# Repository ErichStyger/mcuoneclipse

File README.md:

mcuoneclipse
============

McuOnEclipse Processor Expert components and example projects.
C:\ProgramData\Processor Expert\CWMCU_PE5_00\beans

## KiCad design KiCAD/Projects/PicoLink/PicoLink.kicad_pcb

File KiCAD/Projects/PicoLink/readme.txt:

KiCAD and enclosure design files for a RP2040 based debug probe (PicoLink).
See https://github.com/ErichStyger/mcuoneclipse/tree/master/KiCAD/Projects/PicoLink

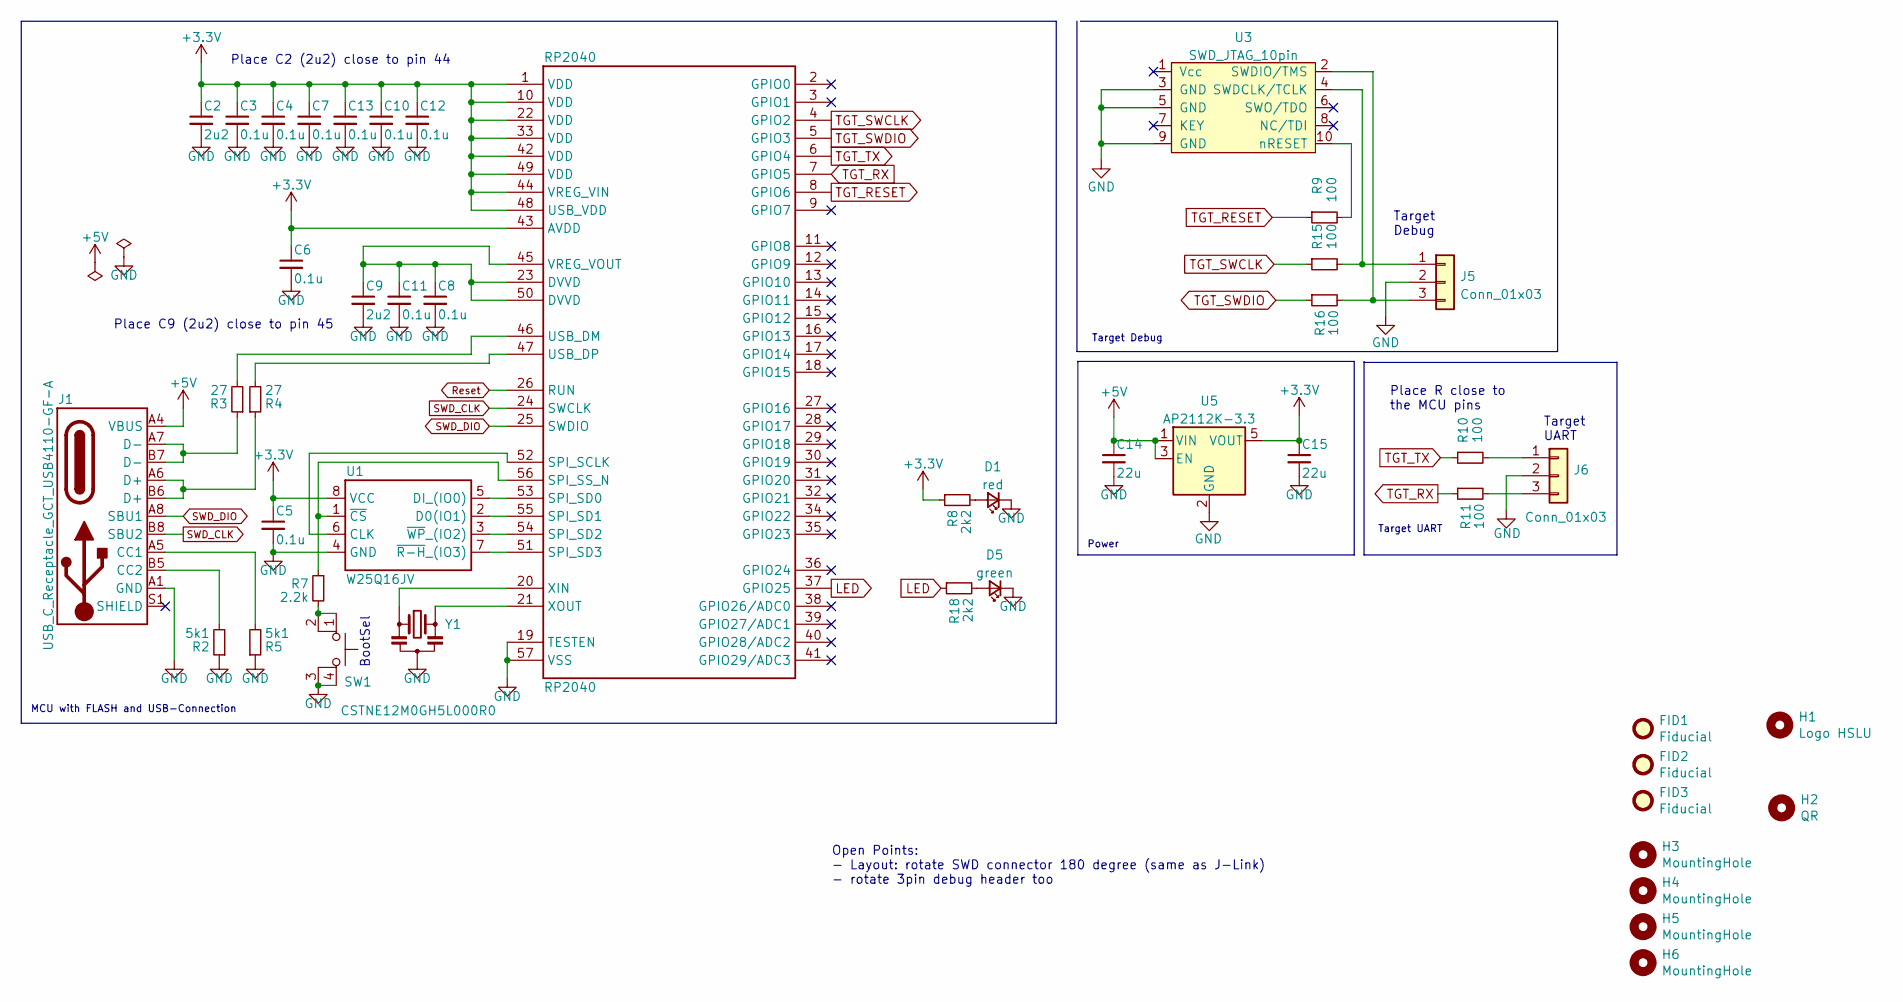
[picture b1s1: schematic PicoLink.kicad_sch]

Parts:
C2, C9: 2u2; C_0603_1608Metric; MFR# CC0402MRX5R6BB225; mouser# 603-CC402MRX5R6BB225
C3, C4, C6, C7, C8, C10, C11, C12, C13: 0.1u; C_0603_1608Metric; MFR# C0402C104K8RAC7867; mouser# 80-C0402C104K8R7867
C5: 0.1u; C_0603_1608Metric; MFR# CC0603KRX7R8BB104; mouser# 603-CC603KRX7R8BB104
C14, C15: 22u; C_0805; MFR# CL21A226MOQNNNE; mouser# 187-CL21A226MOQNNNE
D1: red; LED_0603
D5: green; LED_0603
FID1, FID2, FID3: Fiducial; Fiducial_1mm_Mask2mm
H1: Logo HSLU; Hochschule_Luzern_New
H2: QR; QR_McuOnEclipse_Silkscreen
H3, H4, H5, H6: MountingHole; MountingHole_2.7mm_M2.5
J1: USB_C_Receptacle_GCT_USB4110-GF-A; MFR# USB4110-GF-A; mouser# 640-USB4110-GF-A
J5, J6: Conn_01x03; PinHeader_1x03_P2.54mm_Vertical
R2, R5: 5k1; R_0603_1608Metric; MFR# RC0603JR-075K6L; mouser# 603-RC0603JR-075K6L
R3, R4: 27; R_0603_1608Metric; MFR# RC0603JR-0727RL; mouser# 603-RC0603JR-0727RL
R7: 2.2k; R_0603_1608Metric; MFR# RC0603JR-071KL; mouser# 603-RC0603JR-071KL
R8, R18: 2k2; R_0603_1608Metric; MFR# RC0603JR-071KL; mouser# 603-RC0603JR-071KL
R9, R10, R11, R15, R16: 100; R_0603_1608Metric; MFR# RC0603JR-071KL; mouser# 603-RC0603JR-071KL
RP2040: RP2040; QFN-56-1EP_7x7mm_P0.4mm_EP3.2x3.2mm; MFR# RPI Chip RP2040-7-500; mouser# 358-RP2040CHIP-7-500
SW1: 434123025826_BTN
U1: W25Q16JV; USON_2x3x0.6mm; MFR# W25Q16JVUXIQ TR; mouser# 454-W25Q16JVUXIQTR
U3: SWD_JTAG_10pin; SWD_Pin_Header_Straight_2x05_Pitch1.27mm_SMD
U5: AP2112K-3.3; IC-SOT25; mouser# 621-AP2112K-3.3TRG1
Y1: CSTNE12M0GH5L000R0; Resonator_SMD_Murata_CSTxExxV-3Pin_3.0x1.1mm; MFR# CSTNE12M0GH5L000R0; mouser# 81-CSTNE12M0GH5L000R

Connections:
+3.3V: C2.1, C3.1, C4.1, C5.1, C6.1, C7.1, C10.1, C12.1, C13.1, C15.1, R8.1, RP2040.1 (VDD), RP2040.10 (VDD), RP2040.22 (VDD), RP2040.33 (VDD), RP2040.42 (VDD), RP2040.43 (AVDD), RP2040.44 (VREG_VIN), RP2040.48 (USB_VDD), RP2040.49 (VDD), U1.8 (VCC), U5.5 (VOUT)
+5V: C14.1, J1.A4 (VBUS), J1.A9 (VBUS), J1.B4 (VBUS), J1.B9 (VBUS), U5.1 (VIN), U5.3 (EN)
GND: C2.2, C3.2, C4.2, C5.2, C6.2, C7.2, C8.2, C9.2, C10.2, C11.2, C12.2, C13.2, C14.2, C15.2, D1.1 (K), D5.1 (K), J1.A1 (GND), J1.A12 (GND), J1.B1 (GND), J1.B12 (GND), J5.2, J6.2, R2.1, R5.1, RP2040.19 (TESTEN), RP2040.57 (VSS), SW1.3 (K), SW1.4 (A), U1.4 (GND), U3.3 (GND), U3.5 (GND), U3.9 (GND), U5.2 (GND), Y1.2
LED: R18.1, RP2040.37 (GPIO25)
unnamed: C8.1, C9.1, C11.1, RP2040.23 (DVVD), RP2040.45 (VREG_VOUT), RP2040.50 (DVVD)
unnamed: D1.2 (A), R8.2
unnamed: D5.2 (A), R18.2
unnamed: J1.A5 (CC1), R5.2
unnamed: J1.A6 (D+), J1.B6 (D+), R4.1
unnamed: J1.A7 (D-), J1.B7 (D-), R3.1
unnamed: J1.B5 (CC2), R2.2
unnamed: J5.1, R15.2, U3.4 (SWDCLK/TCLK)
unnamed: J5.3, R16.2, U3.2 (SWDIO/TMS)
unnamed: J6.1, R10.2
unnamed: J6.3, R11.2
unnamed: R3.2, RP2040.46 (USB_DM)
unnamed: R4.2, RP2040.47 (USB_DP)
unnamed: R7.1, RP2040.56 (SPI_SS_N), U1.1 (~CS)
unnamed: R7.2, SW1.1, SW1.2
unnamed: R9.2, U3.10 (nRESET)
unnamed: RP2040.20 (XIN), Y1.1
unnamed: RP2040.21 (XOUT), Y1.3
unnamed: RP2040.51 (SPI_SD3), U1.7 (~R-H_(IO3))
unnamed: RP2040.52 (SPI_SCLK), U1.6 (CLK)
unnamed: RP2040.53 (SPI_SD0), U1.5 (DI_(IO0))
unnamed: RP2040.54 (SPI_SD2), U1.3 (~WP_(IO2))
unnamed: RP2040.55 (SPI_SD1), U1.2 (D0(IO1))
Reset: RP2040.26 (RUN)
SWD_CLK: J1.B8 (SBU2), RP2040.24 (SWCLK)
SWD_DIO: J1.A8 (SBU1), RP2040.25 (SWDIO)
TGT_RESET: R9.1, RP2040.8 (GPIO6)
TGT_RX: R11.1, RP2040.7 (GPIO5)
TGT_SWCLK: R15.1, RP2040.4 (GPIO2)
TGT_SWDIO: R16.1, RP2040.5 (GPIO3)
TGT_TX: R10.1, RP2040.6 (GPIO4)

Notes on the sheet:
Open Points: - Layout: rotate SWD connector 180 degree (same as J-Link) - rotate 3pin debug header too
Target Debug
MCU with FLASH and USB-Connection
Target Debug
Target UART
Place R close to the MCU pins
Target UART
Place C2 (2u2) close to pin 44
Place C9 (2u2) close to pin 45
Power
BootSel

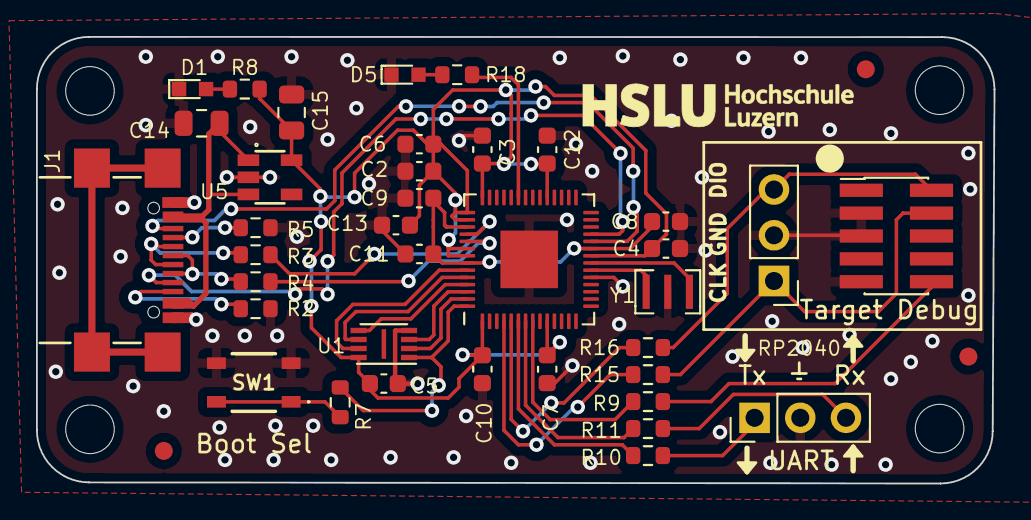
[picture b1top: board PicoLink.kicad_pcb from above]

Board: 2 copper layers, 53.2 x 24.8 mm, 46 parts (1 on the bottom side), 34 nets.

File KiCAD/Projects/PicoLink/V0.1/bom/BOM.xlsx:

Item | Qty | Reference(s) | Value | LibPart | Footprint | Datasheet | MFR | MFR# | digikey# | mouser# | Price 1 (CHF) | Price Total
1 | 2 | C2, C9 | 2u2 | Device:C_Small | Capacitor_SMD:C_0603_1608Metric | ~ | Yageo | CC0402MRX5R6BB225 |  | 603-CC402MRX5R6BB225 | 0.02 | 0.04
2 | 10 | C3, C4, C5, C6, C7, C8, C10, C11, C12, C13 | 0.1u | Device:C_Small | Capacitor_SMD:C_0603_1608Metric | ~ | Yageo | CC0603KRX7R8BB104 |  | 603-CC603KRX7R8BB104 | 1.2999999999999999E-2 | 0.13
3 | 2 | C14, C15 | 22u | Device:C_Small | McuOnEclipse:C_0805 | ~ | Samsung | CC0603KRX7R8BB104 |  | 603-CC603KRX7R8BB104 | 1.2999999999999999E-2 | 2.5999999999999999E-2
4 | 1 | D1 | red | Device:LED_Small | McuOnEclipse:LED_0603 | ~ | Vishay Semiconductors | VLMS1300-GS08 |  | 78-VLMS1300-GS08 | 9.6000000000000002E-2 | 9.6000000000000002E-2
5 | 1 | D5 | green | Device:LED_Small | McuOnEclipse:LED_0603 | ~ | Vishay Semiconductors | VLMTG1300-GS08 |  | 78-VLMTG1300-GS08 | 0.191 | 0.191
6 | 3 | H4, H5, H6 | MountingHole | Mechanical:MountingHole | MountingHole:MountingHole_2.7mm_M2.5 | ~ |  |  |  |  |  | 0
7 | 1 | J1 | USB_C_Receptacle_GCT_USB4110-GF-A | McuOnEclipse:USB_C_Receptacle_GCT_USB4110-GF-A | McuOnEclipse:USB_C_Receptacle_GCT_USB4110-GF-A | ${KICAD_USER_DATASHEET_DIR}\connector\USB-C-Buchse - GCT USB4110.pdf | GCT | USB4110-GF-A |  | 640-USB4110-GF-A | 0.86 | 0.86
8 | 2 | J5, J6 | Conn_01x03 | Connector_Generic:Conn_01x03 | Connector_PinHeader_2.54mm:PinHeader_1x03_P2.54mm_Vertical | ~ |  |  |  | 571-3-826629-6 | 0.23499999999999999 | 0.47
9 | 2 | R2, R5 | 5k1 | Device:R_Small | Resistor_SMD:R_0603_1608Metric | ~ | Yageo | RC0603JR-075K1L |  | 603-RC0603JR-075K1L | 8.0000000000000002E-3 | 1.6E-2
10 | 2 | R3, R4 | 27 | Device:R_Small | Resistor_SMD:R_0603_1608Metric | ~ | Yageo | RC0603JR-0727RL |  | 603-RC0603JR-0727RL | 6.0000000000000001E-3 | 1.2E-2
11 | 3 | R7, R8, R18 | 2k2 | Device:R_Small | Resistor_SMD:R_0603_1608Metric | ~ | Yageo | RC0603JR-072K2L |  | 603-RC0603JR-072K2L | 6.0000000000000001E-3 | 1.8000000000000002E-2
12 | 5 | R9, R10, R11, R15, R16 | 100 | Device:R_Small | Resistor_SMD:R_0603_1608Metric | ~ | Yageo | RC0075JR-07100RL |  | 603-RC0075JR-07100RL | 6.0000000000000001E-3 | 0.03
13 | 1 | RP2040 | RP2040 | McuOnEclipse:RP2040 | McuOnEclipse:QFN-56-1EP_7x7mm_P0.4mm_EP3.2x3.2mm | ${KICAD_USER_DATASHEET_DIR}\ic\RP2040.pdf | Raspberry Pi | RPI Chip RP2040-7-500 |  | 358-RP2040CHIP-7-500 | 0.93100000000000005 | 0.93100000000000005
14 | 1 | SW1 | 434123025826_BTN | Switch:SW_MEC_5E | McuOnEclipse:434123025826_BTN | http://www.apem.com/int/index.php?controller=attachment&id_a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 | Würth Elektronik | 434123025826 | 732-13662-1-ND |  | 0.45 | 0.45
15 | 1 | U1 | W25Q16JV | McuOnEclipse:W25Q16JV | McuOnEclipse:USON_2x3x0.6mm | ${KICAD_USER_DATASHEET_DIR}/ic/Flash SPI - W25Q16JV.pdf | Winbond | 434123025826 |  | 454-W25Q16JVUXIQTR | 0.439 | 0.439
16 | 1 | U3 | SWD_JTAG_10pin | McuOnEclipse:SWD_JTAG_10pin | McuOnEclipse:SWD_Pin_Header_Straight_2x05_Pitch1.27mm_SMD |  | Amphenol FCI | 20021121-00010C4LF |  | 649-202112100010C4LF | 0.69399999999999995 | 0.69399999999999995
17 | 1 | U5 | AP2112K-3.3 | Regulator_Linear:AP2112K-3.3 | McuOnEclipse:IC-SOT25 | https://www.diodes.com/assets/Datasheets/AP2112.pdf | Diodes Incorporated | AP2112K-3.3TRG1 |  | 621-AP2112K-3.3TRG1 | 0.17299999999999999 | 0.17299999999999999
18 | 1 | Y1 | CSTNE12M0GH5L000R0 | McuOnEclipse:CSTNE12M0GH5L000R0 | McuOnEclipse:Resonator_SMD_Murata_CSTxExxV-3Pin_3.0x1.1mm | ${KICAD_USER_DATASHEET_DIR}\discrete\Resonator - CSTNE12M0GH5L000R0.pdf | muRata | CSTNE12M0GH5L000R0 |  | 81-CSTNE12M0GH5L000R | 0.20100000000000001 | 0.20100000000000001

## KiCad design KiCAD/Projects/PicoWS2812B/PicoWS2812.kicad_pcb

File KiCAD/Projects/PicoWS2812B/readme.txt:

Board to use the Pico (RP2040) MCU with up to 8 WS2812B LED stripes.

Links:
https://mcuoneclipse.com/2023/04/02/rp2040-with-pio-and-dma-to-address-ws2812b-leds/
https://github.com/ErichStyger/mcuoneclipse/tree/master/Examples/RaspberryPiPico/pico_LedCube

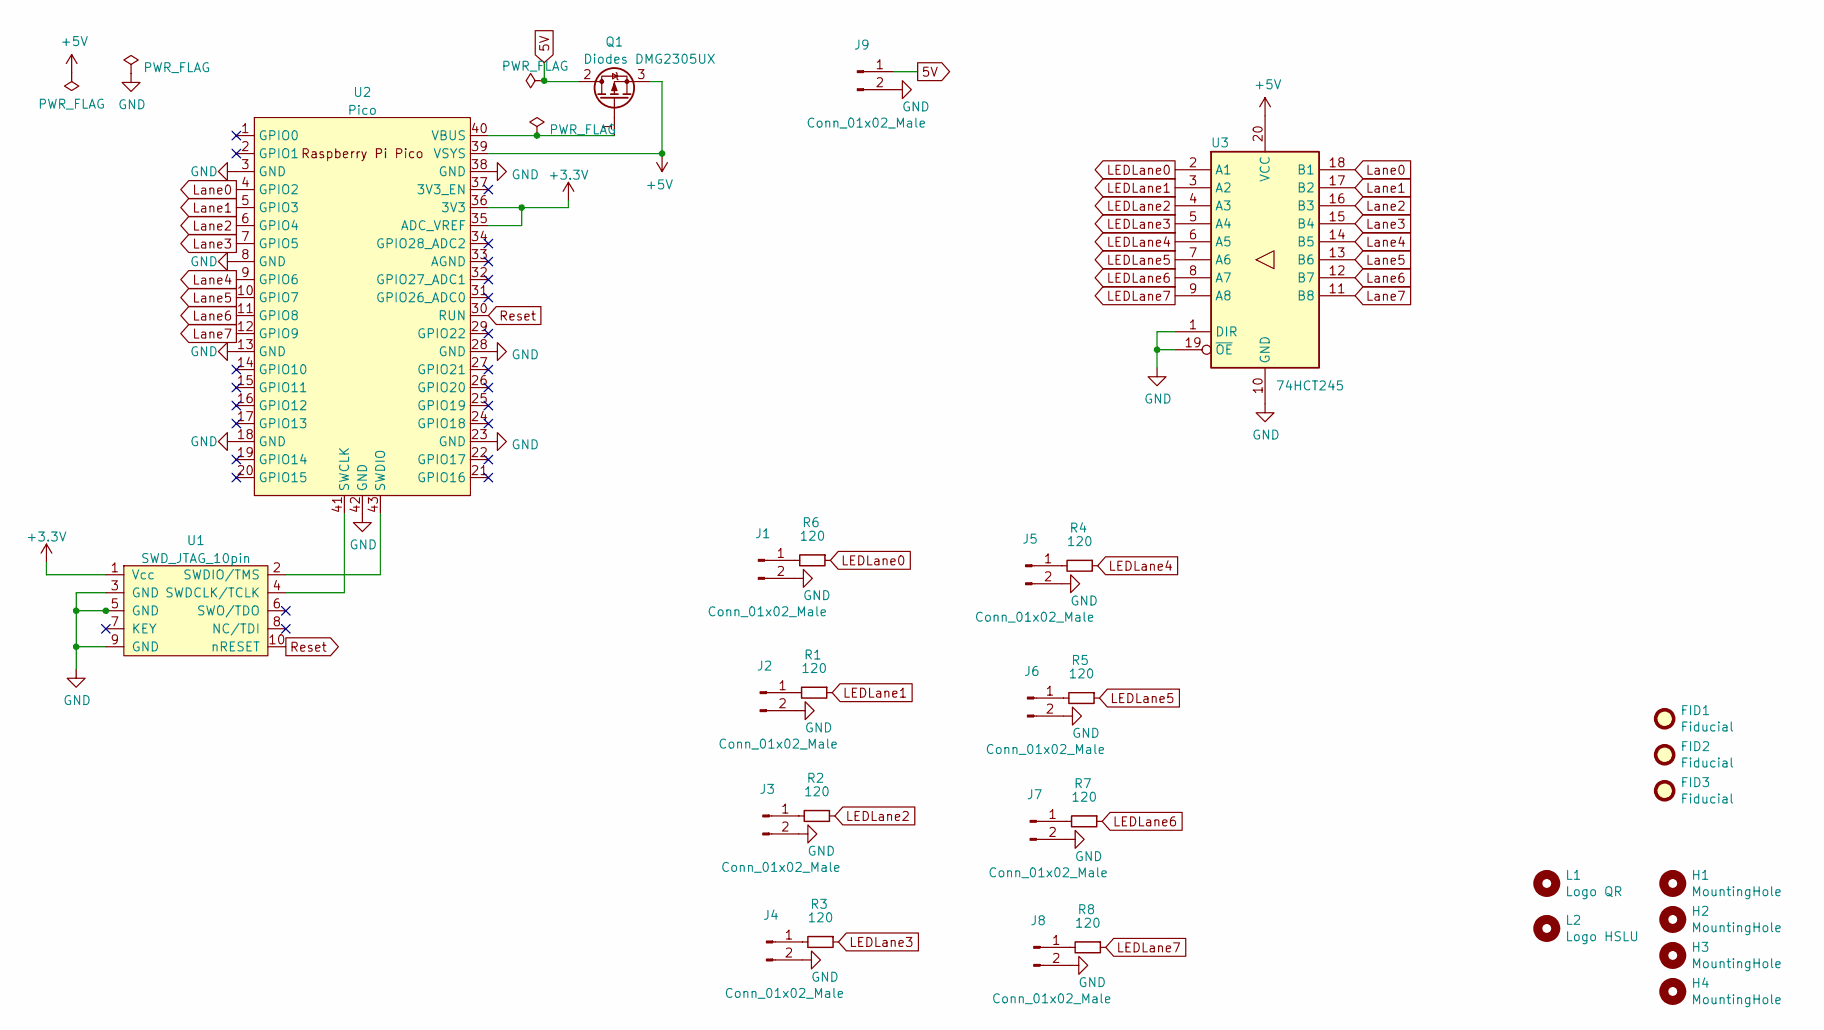
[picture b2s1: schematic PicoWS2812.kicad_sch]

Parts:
FID1, FID2, FID3: Fiducial; Fiducial_1mm_Mask2mm
H1, H2, H3, H4: MountingHole; MountingHole_2.7mm_M2.5
J1, J2, J3, J4, J5, J6, J7, J8, J9: Conn_01x02_Male; PinHeader_1x02_P2.54mm_Horizontal
L1: Logo QR; QR_McuOnEclipse_Silkscreen_9x9mm
L2: Logo HSLU; Hochschule_Luzern_Small
Q1: Diodes DMG2305UX; SOT-23_2T; mouser# 621-DMG2305UX-7
R1, R2, R3, R4, R5, R6, R7, R8: 120; R_0603_1608Metric
U1: SWD_JTAG_10pin; SWD_Pin_Header_Straight_2x05_Pitch1.27mm_SMD
U2: Pico; RPi_Pico_SMD_TH
U3: 74HCT245; SSOP-20_4.4x6.5mm_Pitch0.65mm

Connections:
5V: J9.1, Q1.2 (D)
+3.3V: U1.1 (Vcc), U2.35 (ADC_VREF), U2.36 (3V3)
+5V: Q1.3 (S), U2.39 (VSYS), U3.20 (VCC)
GND: J1.2, J2.2, J3.2, J4.2, J5.2, J6.2, J7.2, J8.2, J9.2, U1.3 (GND), U1.5 (GND), U1.9 (GND), U2.3 (GND), U2.8 (GND), U2.13 (GND), U2.18 (GND), U2.23 (GND), U2.28 (GND), U2.38 (GND), U2.42 (GND), U3.1 (DIR), U3.10 (GND), U3.19 (~OE)
LEDLane0: R6.1, U3.2 (A1)
LEDLane1: R1.1, U3.3 (A2)
LEDLane2: R2.1, U3.4 (A3)
LEDLane3: R3.1, U3.5 (A4)
LEDLane4: R4.1, U3.6 (A5)
LEDLane5: R5.1, U3.7 (A6)
LEDLane6: R7.1, U3.8 (A7)
LEDLane7: R8.1, U3.9 (A8)
Lane0: U2.4 (GPIO2), U3.18 (B1)
Lane1: U2.5 (GPIO3), U3.17 (B2)
Lane2: U2.6 (GPIO4), U3.16 (B3)
Lane3: U2.7 (GPIO5), U3.15 (B4)
Lane4: U2.9 (GPIO6), U3.14 (B5)
Lane5: U2.10 (GPIO7), U3.13 (B6)
Lane6: U2.11 (GPIO8), U3.12 (B7)
Lane7: U2.12 (GPIO9), U3.11 (B8)
unnamed: J1.1, R6.2
unnamed: J2.1, R1.2
unnamed: J3.1, R2.2
unnamed: J4.1, R3.2
unnamed: J5.1, R4.2
unnamed: J6.1, R5.2
unnamed: J7.1, R7.2
unnamed: J8.1, R8.2
unnamed: Q1.1 (G), U2.40 (VBUS)
unnamed: U1.2 (SWDIO/TMS), U2.43 (SWDIO)
unnamed: U1.4 (SWDCLK/TCLK), U2.41 (SWCLK)
Reset: U1.10 (nRESET), U2.30 (RUN)

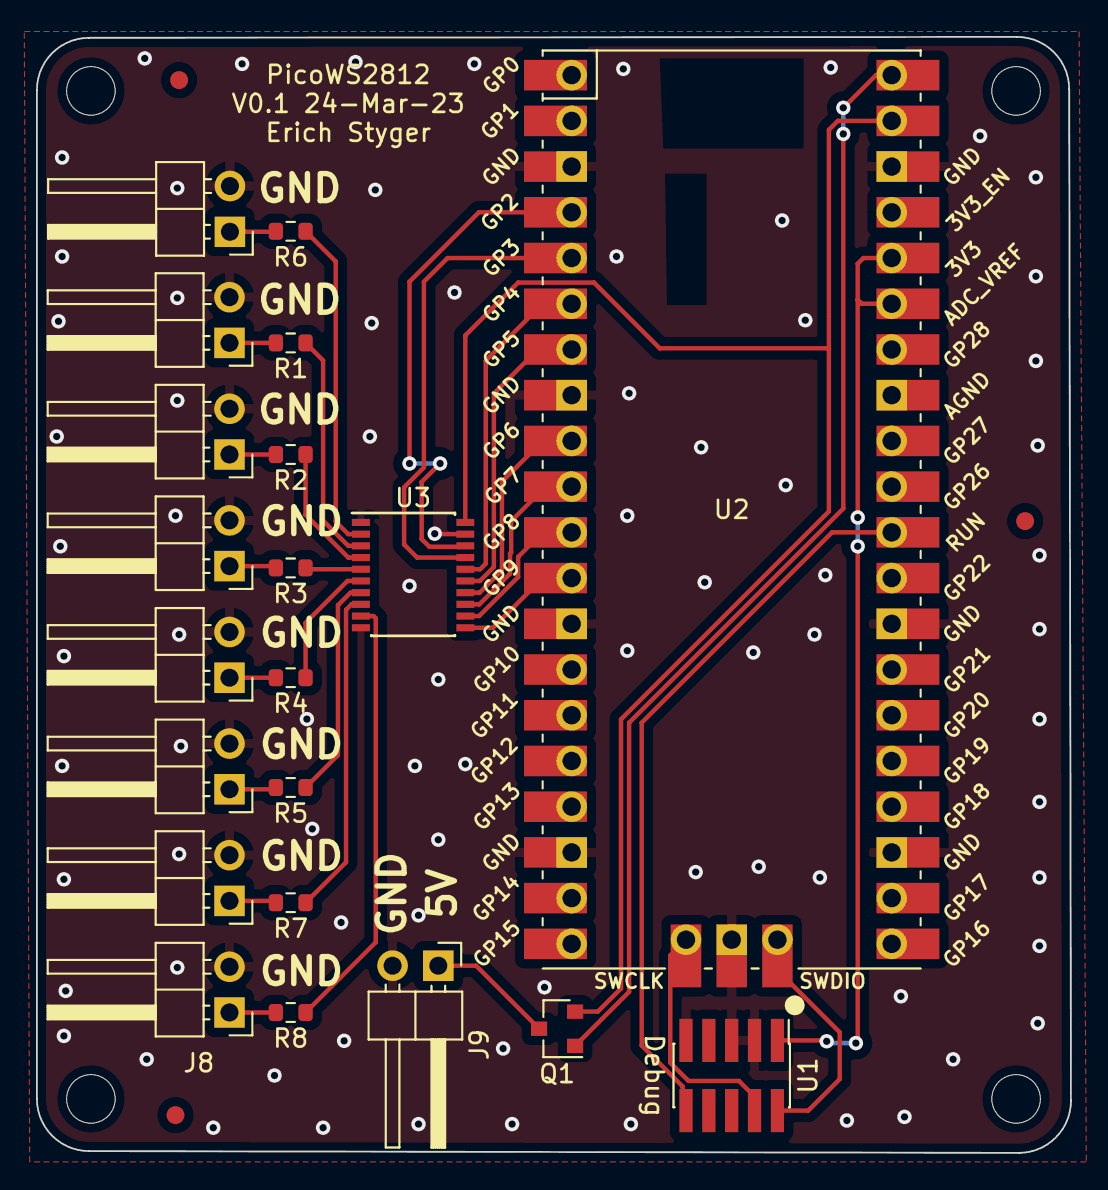
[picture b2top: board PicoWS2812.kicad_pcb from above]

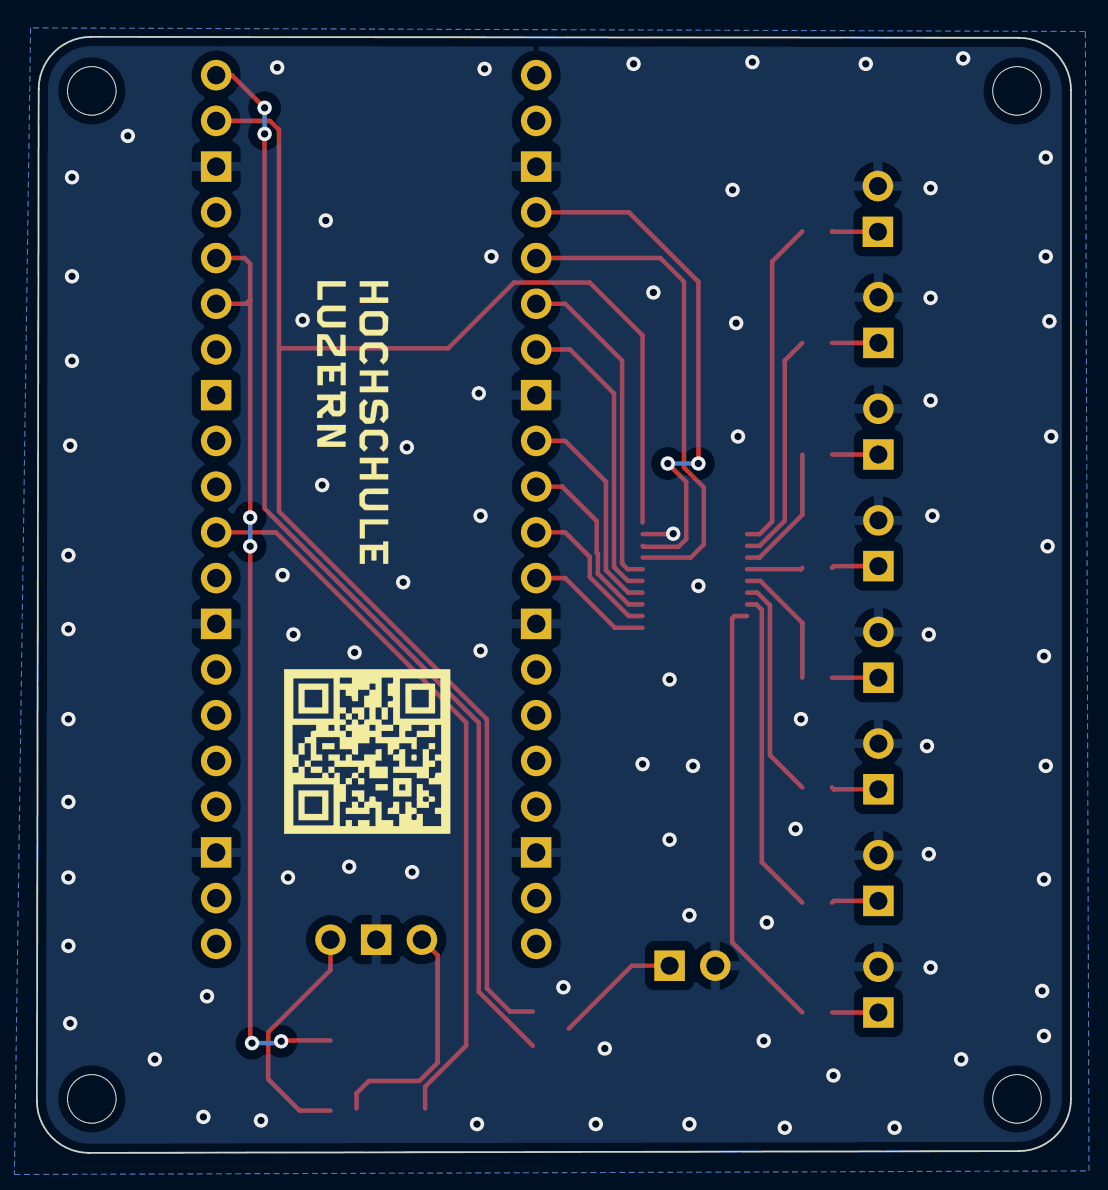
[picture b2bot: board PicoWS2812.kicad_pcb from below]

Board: 2 copper layers, 57.4 x 62.0 mm, 30 parts (2 on the bottom side), 32 nets.

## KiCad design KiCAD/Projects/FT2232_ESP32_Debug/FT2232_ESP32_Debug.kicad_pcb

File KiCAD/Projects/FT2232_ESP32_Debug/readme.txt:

Project to use a FT2232 board to debug the ESP32.

Links:
https://mcuoneclipse.com/2019/10/20/jtag-debugging-the-esp32-with-ft2232-and-openocd/
https://mcuoneclipse.com/2019/11/09/open-source-ftdi-ft2232-jtag-and-uart-adapter-board/

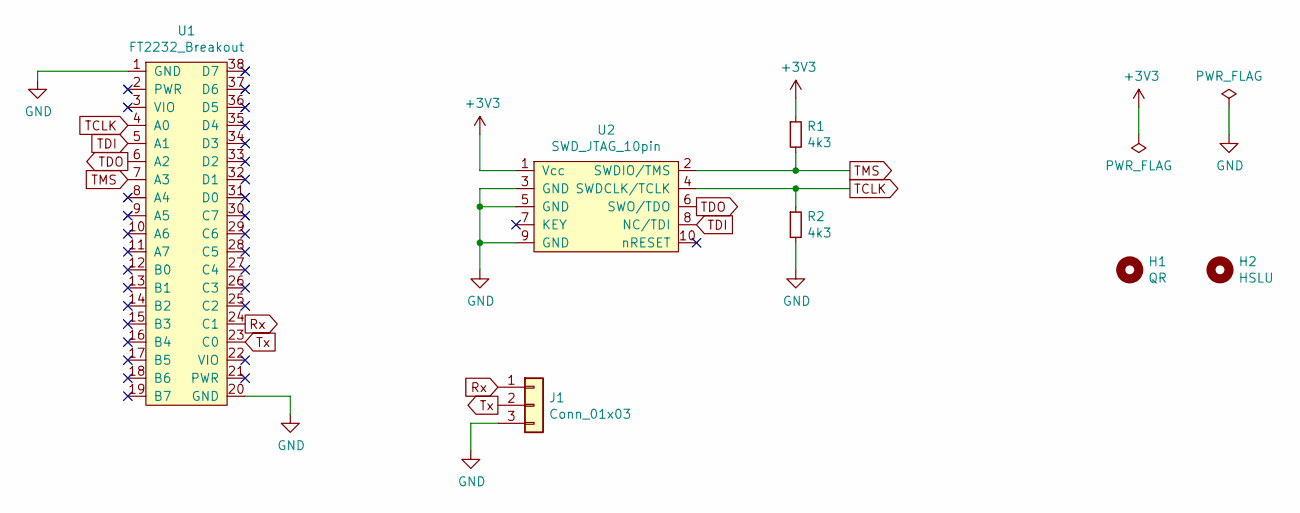
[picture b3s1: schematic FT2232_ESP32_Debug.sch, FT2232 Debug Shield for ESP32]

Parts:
H1: QR; QR_McuOnEclipse_Silkscreen_9x9mm
H2: HSLU; HSLU_Logo_Silkscreen
J1: Conn_01x03; Pin_Header_Straight_1x03_Pitch2.54mm
R1, R2: 4k3; R_0603
U1: FT2232_Breakout; FT2232_Breakout_Pin_Header_Straight_2x19_Pitch2.54mm
U2: SWD_JTAG_10pin; SWD_Pin_Header_Straight_2x05_Pitch1.27mm

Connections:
+3V3: R1.1, U2.1 (Vcc)
GND: J1.3, R2.2, U1.1 (GND), U1.20 (GND), U2.3 (GND), U2.5 (GND), U2.9 (GND)
Rx: J1.1, U1.24 (C1)
TCLK: R2.1, U1.4 (A0), U2.4 (SWDCLK/TCLK)
TDI: U1.5 (A1), U2.8 (NC/TDI)
TDO: U1.6 (A2), U2.6 (SWO/TDO)
TMS: R1.2, U1.7 (A3), U2.2 (SWDIO/TMS)
Tx: J1.2, U1.23 (C0)

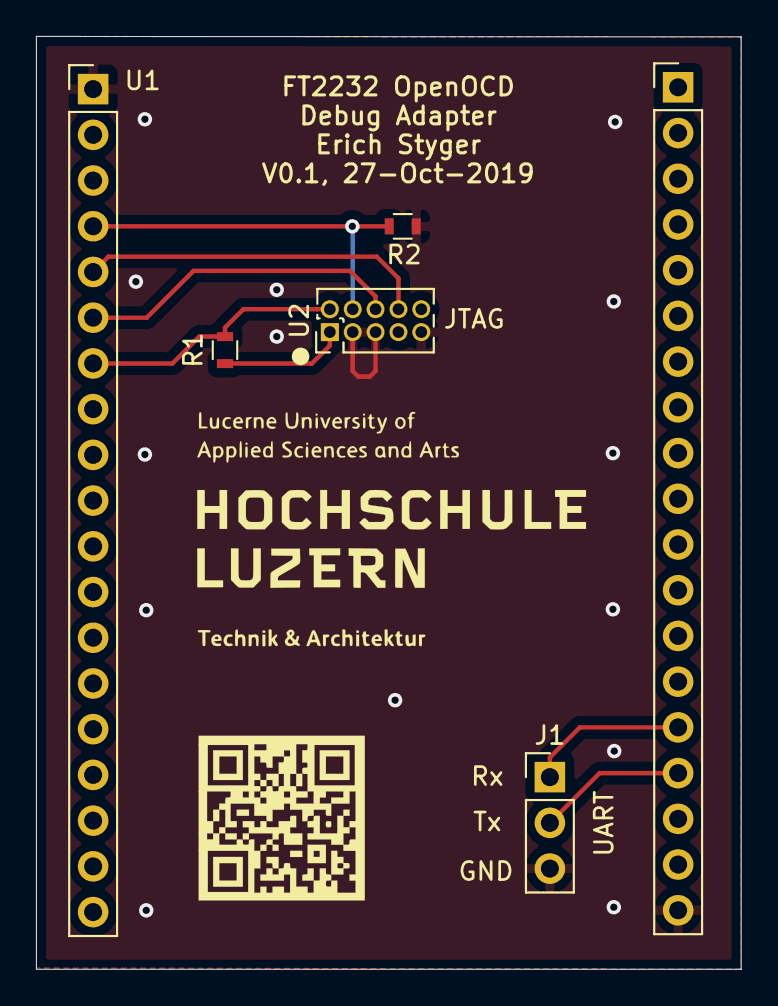
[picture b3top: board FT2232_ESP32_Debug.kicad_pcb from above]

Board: 2 copper layers, 39.1 x 51.8 mm, 7 parts (0 on the bottom side), 8 nets.

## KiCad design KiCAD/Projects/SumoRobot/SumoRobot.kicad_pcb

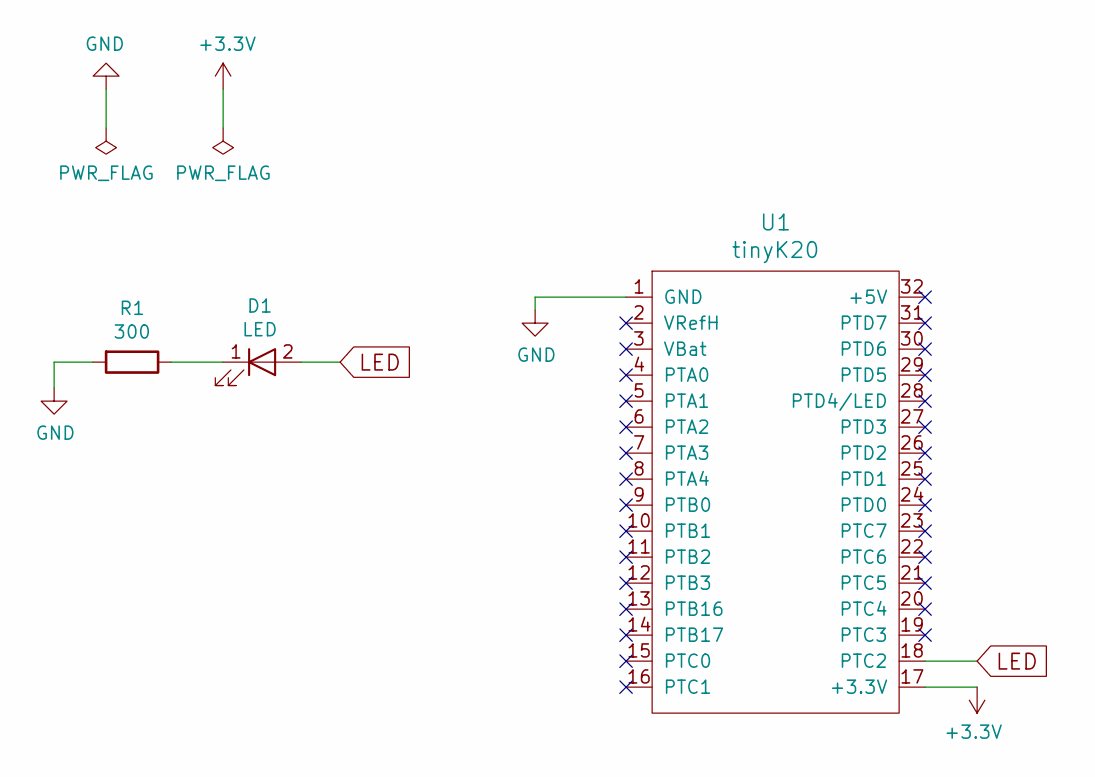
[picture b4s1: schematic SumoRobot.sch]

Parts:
D1: LED; LED_0805
R1: 300; R_0805
U1: tinyK20; DIP-32_W15.24mm

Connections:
+3V3: U1.17 (+3.3V)
GND: R1.2, U1.1 (GND)
LED: D1.2 (A), U1.18 (PTC2)
unnamed: D1.1 (K), R1.1

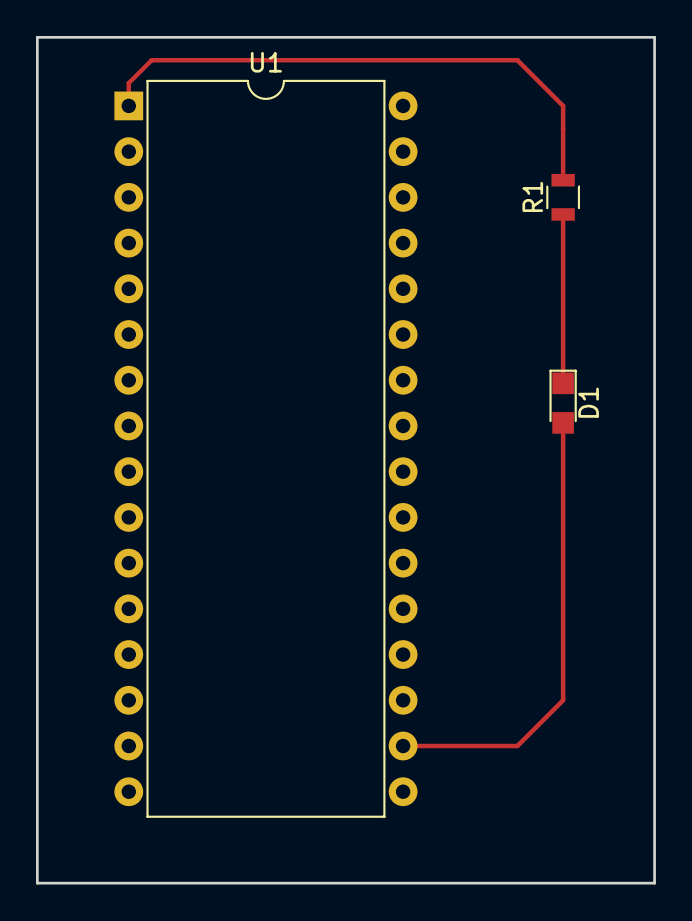
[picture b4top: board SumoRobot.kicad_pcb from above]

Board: 2 copper layers, 34.3 x 47.0 mm, 3 parts (0 on the bottom side), 3 nets.

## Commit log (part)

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2024-01-26 updated projects
2024-01-28 added particle animation
2024-01-28 updated with latest components
2024-01-28 more updates to latest components
2024-01-29 added heap protector
2024-01-29 updated animation
2024-01-29 added burst, not impleented yet
2024-02-06 updated with latests SDK
2024-02-21 updated version number
2024-02-21 added animation
2024-02-22 updated to latest IDE, moved to CMake Presets
2024-03-07 fixed include header file name
2024-03-07 added more spacer
2024-03-07 fixed header file name
2024-03-07 added SDK internal RTC
2024-03-08 disabled unused function
2024-03-11 making it generic
2024-03-11 fixed name spelling
2024-03-11 updated SDK
2024-03-11 added new font
2024-03-11 fixed typo
2024-03-12 fixed folder spellng for LInux
2024-03-12 added MCU-Link components
2024-03-12 updated project
2024-03-12 updated symbol library
2024-03-15 added clock functionality
2024-03-21 updated flip-dot project
2024-03-23 updated KiCad models and library
2024-03-24 updated symbols and added 3D models
2024-03-24 updated thermal pad
2024-03-24 fixed warnings
2024-03-24 new symbols
2024-04-06 enabled watchdog timer
2024-04-06 updates for business card project
2024-04-12 footprint changed for 6/6 mil
2024-04-17 UID for LPC804
2024-04-17 merged fix for STM32
2024-04-23 added new footprint for TDK VLCF024
2024-04-23 extended support for LPC804
2024-04-24 updated footprints
2024-04-24 added 3D models
2024-04-27 updated projects with using the CMSIS-Core library.
2024-05-05 disabled for Heap3
2024-05-05 turned on BLE
2024-05-05 fix for subcommands > 256
2024-05-05 upgraded LittleFS
2024-05-07 moved from AEMBS project
2024-05-07 fixed readme
2024-05-16 fixed FreeRTOS warnings
2024-05-16 fixed status output
2024-05-16 updated with new IDE and SDK
2024-05-16 new board with 16 LEDs, updated LED animation
2024-05-16 merged with latest git version
2024-05-17 updated year
2024-05-19 updated for latest SDKs
2024-05-19 merged McuLib
2024-05-21 added LPC804 low power example
2024-05-22 updated settings and added link to article
2024-05-22 cleaned project
2024-05-31 updated projects with SDK
2024-05-31 added setting for LED
2024-06-11 fixed handling of event bits
2024-06-13 updated footprints for 0.22mm gap between pads for black soldermask
2024-06-13 updated for 11.9.1
2024-06-13 updated for IDE 11.9.1
2024-06-13 added SDK RT685 project
2024-06-13 working debug session
2024-06-13 updated with config tools
2024-06-13 added pyOCD launch config
2024-06-13 using McuLib
2024-06-13 added patched DFP file
2024-06-19 added ESA demo mode
2024-06-19 added comments
2024-06-21 added option for retargeting
2024-06-21 fixed compiler warning
2024-06-21 updated gcov examples with latest IDE and SDK
2024-06-26 less power for ESA demo
2024-06-29 enabled for C++
2024-06-30 added hardware part
2024-06-30 added 3D printing files
2024-07-01 updated RTC driver
2024-07-03 improved RTC driver
2024-07-03 fixed CMSIS naming of ISRs for RP2040
2024-07-05 improved animation
2024-07-10 updated for linux usage
2024-07-10 cleanup
2024-07-23 updated projects with new IDE
2024-07-24 updated USB stack
2024-07-24 updated mex
2024-07-24 updated projects with new SDKs
2024-07-24 removed part support
2024-07-24 updated coverage and projects
2024-07-24 GPIO and LED support for MCX (N947)
2024-07-24 added MCX project
2024-07-29 changed to newlib-nano
2024-07-29 added sdk project
2024-07-29 updated McuLib for MCX
2024-07-31 added standalone cov converter
2024-08-02 need to align FreeRTOS information struct for LinkServer debugging at higher gcc optimizations.
2024-08-02 upcated gcov implementation
2024-08-02 updated projects with new IDE and SDK
2024-08-02 using OLED without GUI
2024-08-08 updated with new components
2024-08-15 project cleanup, verified bm gcov with K64
2024-08-15 added LEDs
2024-08-15 undo temporary change
2024-08-15 added GPIO release and NeoPixels for Raspy Interface
2024-08-16 using latest gcc
2024-08-16 updated for gcc13
2024-08-16 initial C++ project
2024-08-16 moved to IDE 11
2024-08-16 added McuLib
2024-08-16 added C++ interface
2024-08-16 adding gcov support
2024-08-17 added blinky
2024-08-17 fixed include order for i.MX
2024-08-17 added MEX
2024-08-17 cleanup and added link to article.
2024-08-23 updated configurations
2024-08-25 added SEGGER SystemView example for Data Plot functionality.
2024-08-26 Updated SystemView to v3.56
2024-08-26 merged with PEx driver
2024-08-27 switching back ot anonymous union
2024-08-27 working with integer: problem was using a scaling factor of zero.
2024-08-27 updated debug probe settings
2024-08-27 added newline
2024-08-27 changed to signed data type
2024-08-27 more more with SEGGER sources
2024-08-27 added Team Project Set
2024-08-28 updated SDK version
2024-08-29 updated launch settings
2024-09-05 using non-anonymous union
2024-09-26 added MCXN236 base project
2024-09-26 working blinky
2024-09-26 added RTT
2024-09-26 add RTT
2024-09-27 cleanup and extended project
2024-09-30 removed freestanding
2024-09-30 updated probe firmware
2024-10-03 updated SDK and probe settings
2024-10-03 initial usb host project
2024-10-03 added usb files
2024-10-04 moved files
2024-10-04 added CMake files
2024-10-04 fixed linking libraries
2024-10-04 working shell
2024-10-04 added board and LED support
2024-10-04 added header
2024-10-04 enabling usb host
2024-10-04 working CDC on device side
2024-10-04 slowed down debug output
2024-10-04 working host mode HID with device CDC
2024-10-14 change for SDK 2.0.0
2024-10-20 updated with latest McuLib
2024-10-22 fixed directory name
2024-10-23 commit added debug output
2024-10-23 working with standard pico board and USB host breakout
2024-10-23 re-added CDC host support
2024-10-23 added exit call
2024-10-23 added CDC host
2024-10-24 added footprint
2024-10-31 fixed format string
2024-11-01 fixed include for sdk 2.0.0
2024-11-01 using tinyk22 USB stack
2024-11-04 adding new module McuShellCdcDevice
2024-11-12 updated launch settings for new McuLink probe
2024-11-18 fixed SDK version
2024-11-20 added picotool windows binary for SDK 2.0.0.
2024-11-24 fixed McuLink location
2024-11-24 udpated debug probe
2024-11-24 updated description
2024-12-04 added new modules
2024-12-06 merged McuLib with new version from master
2024-12-06 removing batch files
2024-12-07 ported project to SDK 2.0.0
2024-12-09 updated with new SDK 2.0.0
2024-12-11 updated McuLib
2024-12-11 using new SDK
2024-12-11 cleanup, not needed anymore
2024-12-14 merged project with sensor project, VS Code only
2024-12-23 Added new animations
2024-12-24 updated launch configs
2024-12-27 Added helicopter and pyramid animation
2025-01-13 added missing include
2025-01-14 added semihosting example
2025-01-14 merged McuLib and updated projects
2025-01-14 updated semihosting
2025-01-15 updated projects and extended documentation
2025-01-15 extended buffer size
2025-01-15 disabled semihosting testing
2025-01-17 added console processing
2025-01-17 extended semihosting for latest LinkServer
2025-01-17 updated with new SDK
2025-01-17 extended semihosting with shell
2025-01-21 initial project
2025-01-22 updated McuLib location
2025-01-22 extended implementation with RNet, RTC and LEDs
2025-01-24 increased stack size
2025-01-24 enabled SWO
2025-01-24 testing SWO output clocking
2025-01-31 added sensor code
2025-02-04 updated SDKs
2025-02-12 added %n handling
2025-02-12 extended comment
2025-02-12 added semihosting prefix handling
2025-02-13 migrating to McuLib sub-repo
2025-02-13 using submodule for McuLib
2025-02-18 changed debug probe
2025-02-27 Updated with latest component versions
2025-02-27 initial project, based on the work of Peter
2025-02-27 converted with 24.12 IDE
2025-02-27 going to ignore that file
2025-02-27 using common McuLib
2025-03-06 updated SDK for secure/non-secure demo
2025-03-10 had to fix launch configs
2025-03-13 added Adafruit Feather project
2025-03-13 added shell support
2025-03-19 using 8 MByte of FLASH
2025-03-19 enabled RTT
2025-03-19 working WS2812B
2025-03-19 disabled normal LED support
2025-03-26 updated symbols
2025-03-26 added nRF and V_AUX support
2025-04-07 added J-Link script
2025-04-07 added standalone SDK project
2025-04-07 cleanup and added readme
2025-04-07 cleanup, fixed flash task
2025-04-07 added git to the list
2025-04-30 changed probe
2025-05-16 added test code for UART2
2025-05-16 muxing extra GPIO pin
2025-05-25 fixed typos
2025-05-25 new version
2025-06-18 added setting for SonarQube
2025-06-18 updated library
2025-06-18 better USB performance
2025-06-18 sending presence detection message
2025-06-30 using new McuLib
2025-07-07 excluded folders for bare-metal mode
2025-07-07 enabled semihosting with file I/O
2025-07-18 added new launch configuration
2025-07-18 added RAM target
2025-07-18 renamed main file
2025-08-10 added top part
2025-08-10 removed freestanding option
2025-08-10 new McuLib
2025-08-11 merged project and updated to latest version
2025-08-25 merged projectes
2025-08-25 added VS Code project for LPC55S69
2025-08-25 enabled application
2025-08-27 updated SDK version information
2025-08-28 adding USB HID project
2025-08-28 updated debug config and working blinky
2025-08-28 added HID example
2025-08-28 added LED blinky
2025-09-01 working USB HID
2025-09-22 cleanup and added environment setup
2025-10-01 added comment
2025-10-01 new McuLib release
2025-10-13 updated SDK and changed debug probe
2025-10-15 updated new debug probe settings
2025-10-15 added standalone Rust Embassy example
2025-10-24 Updated version of McuLib
2025-10-24 added information to readme
2025-10-24 improved USB CDC performance and blocking
2025-10-24 using cortex delay
2025-10-24 run analyzer on save
2025-10-28 updated symbols for KiCad 9.0
2025-10-28 added project using different external power/voltage/current measurement ICs
2025-10-28 fixed title
2025-10-30 updated footprint
2025-10-30 fixed missing include
2025-11-20 added muxing
2025-11-20 disabled test
2025-11-20 adding new driver for GPé8403
2025-11-20 updated header and added config item
2025-11-20 integrated DAC module driver
2025-11-20 disabled automatic data sending
2025-11-26 reflecting DAC
2025-11-26 working I2C communication
2025-11-27 improved swap macro
2025-11-27 added more functionality, but reading always 0x1111 back from device
2025-12-04 extended sensors, work in progress
2025-12-08 improved DAC handling, prepared for multiple devices
2025-12-08 added support for 2 DAC devices
2025-12-08 renamed launch configs
2025-12-08 fixed bit order
2025-12-08 configured device pins
2025-12-08 configured SPI
2025-12-08 reading more registers
2025-12-08 fixed de-init
2025-12-08 added scaling to values
2025-12-08 extended reading functions
2025-12-08 added shunt handling
2025-12-08 extended driver
2025-12-11 moved power measurement project from internal repo
2025-12-23 integrated contribution of Raul Trrpon driving a bistable relais.
2025-12-25 added design files
2025-12-31 updated comments
2025-12-31 improved name plate
2025-12-31 better fit for more recent PCBs
2025-12-31 updated STL files
2026-01-20 added MCU-Link Pro rugged enclosure
2026-01-20 fixed command handling
2026-01-20 enabled RTT shell interface
2026-02-08 updated design files
2026-03-03 added rugged box project
2026-03-03 added lido reader, starting point
2026-03-04 updated lido parsing
2026-03-04 implemented more reading functionality
2026-04-23 updated KiCad symbols
2026-04-23 finished file reader for LiDo dump files
2026-04-23 updated footprint with PCB drills for standoffs
2026-04-23 enabled tracealyzer
2026-04-24 Update README.txt
    added DeepWiki link
2026-05-05 updated 3D files
2026-05-05 trying out Tracealyzer
2026-05-07 fix: V-002 security vulnerability
    Automated security fix generated by Orbis Security AI
2026-05-15 using common WiFi modules
2026-05-26 udpated McuLib
2026-05-26 updated link
